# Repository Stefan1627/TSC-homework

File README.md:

# TSC-homework - Stefan Calmac 334CC
# InkTime Watch

---

## Block Diagram

```
           [ USB Type-C ]                              [ LiPo Battery (250mAh) ]
                 | 5V VBUS                                      |
                 v                                              |
          +---------------+                                     |
          |               | BAT                                 |
          |    BQ25180    |<------------------------------------+
          | (Charger IC)  |                                     |
          +---------------+                                     v
                 | VSYS                                 +---------------+
                 v                                      |   MAX17048    |
          +---------------+                             | (Fuel Gauge)  |
          |    RT6160     |                             +---------------+
          | (Buck-Boost)  |                                     ^
          +---------------+                                     |
                 | 3.3V System Rail (VDD_3V3)                   |
                 |                                              |
 +---------------+----------------------------------------------+-----+
 |               |                                              |     |
 |               v                                              |     |
 |        +-------------+         I2C Bus                       |     |
 |        |             |<======================================+     |
 |        |             |                                             |
 |        |             |=== I2C ===> [ BMA421 Accelerometer ]        |
 |        |  nRF52840   |                                             |
 |        |    MCU      |=== I2C ===> [ DRV2605L Driver ]-->[ Motor ] |
 |        |             |                                             |
 |        |             |=== SPI ===> [ 1.54" E-paper Display ]       |
 |        |             |                       ^                     |
 |        |             |-- GPIO (Gate)         | VEPD (Switched Pwr) |
 |        +-------------+      |                |                     |
 |          ^  ^  ^  |         v                |                     |
 |          |  |  |  | +---------------+        |                     |
 +---------(|--|--|)-+-|  PFET Switch  |--------+                     |
            |  |  |  | +---------------+                              |
 [Up]-------+  |  |  |                                                |
           [Down] |  +--- [ 2.4GHz Antenna ] - - - BLE - - - [ Companion ]
                  |                                          [   Phone   ]
              [Enter/Esc]
```

---

## Bill of Materials (BOM)

Below is the list of primary active and critical passive components used in this
design. Links are provided to JLCPCB parts (LCSC) and standard datasheets.

| Component / Module | Description | Package / Footprint | Part | Datasheet Link |
:--- | :--- | :--- | :--- | :--- |
| **nRF52840** | Multi-protocol BLE 5.0 Cortex-M4F MCU | AQFN-73 | [C190794](https://jlcpcb.com/partdetail/NordicSemicon-NRF52840_QIAAR/C190794) | [Nordic nRF52840](https://www.nordicsemi.com/Products/nRF52840) |
| **BQ25180YBGR** | I2C Controlled 1A Linear LiPo Charger | DSBGA-8 | [BQ25180YBGR](https://www.ti.com/product/BQ25180/part-details/BQ25180YBGR) | [TI BQ25180](https://www.ti.com/product/BQ25180) |
| **MAX17048G+T10** | Micropower 1-Cell Fuel Gauge | TDFN-8 | [C2682616](https://www.lcsc.com/product-detail/C2682616.html) | [Maxim MAX17048](https://www.analog.com/en/products/max17048.html) |
| **RT6160AWSC** | High-Efficiency Buck-Boost Converter (3.3V) | WLCSP-15 | [C7065276](https://www.lcsc.com/product-detail/C7065276.html) | [Richtek RT6160A](https://www.richtek.com/assets/product_file/RT6160A/DS6160A-02.pdf) |
| **BMA421** | Ultra-Low Power IMU / Step Counter | LGA-12 | [C5242966](https://jlcpcb.com/partdetail/BoschSensortec-BMA421/C5242966) | [Bosch BMA421](https://www.bosch-sensortec.com/products/motion-sensors/imus/bma421/) |
| **DRV2605YZFR** | Haptic Driver for LRA/ERM | DSBGA-9 | [C527464](https://jlcpcb.com/partdetail/C527464) | [TI DRV2605](https://www.ti.com/product/DRV2605) |
| **2450AT18B100E** | 2.4GHz Chip Antenna | 1206 | [C2917717](https://jlcpcb.com/partdetail/JohansonDielectrics-2450AT18B100E/C2917717) | [Johanson 2450AT18B100E](https://www.johansontechnology.com/datasheets/antennas/2450AT18B100.pdf) |
| **USBLC6-2SC6Y** | Very low capacitance ESD protection | SOT-23-6 | [C2969755](https://jlcpcb.com/partdetail/STMicroelectronics-USBLC62SC6Y/C2969755) | [ST USBLC6-2](https://www.st.com/resource/en/datasheet/usblc6-2.pdf) |
| **KH-TYPE-C-16P** | USB Type-C 16-Pin Receptacle | SMD | [C168704](https://jlcpcb.com/partdetail/180087-918418K2022Y40000/C168704) | [Generic USB-C](https://datasheet.lcsc.com/lcsc/1811151641_Korean-Hroparts-Elec-TYPE-C-31-M-12_C165948.pdf) |
| **503480-2400** | 24-Pin FPC Connector (0.5mm pitch) for EPD | SMD |  | [Molex 503480](https://www.molex.com/molex/products/part-detail/ffc_fpc_connectors/5034802400) |
| **DMG2305UX** | P-Channel MOSFET (EPD Power Control) | SOT-23 | [C2940629](https://jlcpcb.com/partdetail/TECHPUBLIC-DMG2305UX/C2940629) | [Diodes DMG2305](https://www.diodes.com/assets/Datasheets/DMG2305UX.pdf) |
| **MBR0530** | Schottky Diode (E-Paper Pump Circuit) | SOD-123 | [C77336](https://jlcpcb.com/partdetail/78464-MBR0530/C77336) | [Onsemi MBR0530](https://www.onsemi.com/pdf/datasheet/mbr0530t1-d.pdf) |
| **TC2030-IDC** | 6-Pin Tag-Connect SWD Interface | PCB Footprint | [Tag-Connect](https://www.tag-connect.com/product/tc2030-idc-nl) | [Tag-Connect TC2030](https://www.tag-connect.com/product/tc2030-idc-6-pin-tag-connect-plug-of-nails-spring-pin-cable-with-ribbon-connector) |

### Passive Components

| Component | Value | Package | Qty | Function |
|-----------|-------|---------|-----|----------|
| Capacitors (decoupling) | 100nF | 0201 | 5 | MCU + peripheral decoupling |
| Capacitors (crystal load) | 12pF | 0201 | 4 | 32MHz + 32.768kHz crystal loads |
| Capacitors (bulk) | 4.7uF | 0402 | 4 | MCU power rail bulk decoupling |
| Capacitors (USB) | 4.7uF | 0402 | 1 | DECUSB capacitor |
| Capacitors (power) | 22uF | 0402 | 2 | RT6160 input capacitors |
| Capacitors (charger) | 1uF | 0402 | 3 | BQ25180 CIN/CSYS/CBAT |
| Capacitors (EPD) | 1uF/50V | 0402 | 9 | E-paper driver capacitors |
| Inductor (DC/DC) | 10uH | 0402 | 1 | nRF52840 REG1 DC/DC inductor |
| Inductor (buck-boost) | 0.47uH | 2012 | 1 | RT6160 power stage inductor |
| Resistors (I2C pull-up) | 10k | 0201 | 2 | I2C SDA/SCL pull-ups |
| Resistors (USB CC) | 5.1k | 0201 | 2 | USB Type-C CC1/CC2 pull-downs |
| Crystals | 32 MHz | 2016 | 1 | HFXO for MCU + radio |
| Crystals | 32.768 kHz | 3215 | 1 | LFXO for RTC timekeeping |

---

## Hardware Description

### MCU - nRF52840

The nRF52840 is the central processing unit of InkTime. It integrates:

- **ARM Cortex-M4F** at 64 MHz with FPU
- **BLE 5.0** (used for time sync, notifications)
- **USB 2.0 Full Speed** (charging detection and firmware updates)
- **1 MB Flash / 256 KB RAM**

All peripherals are connected directly to the nRF52840 via SPI (e-paper display) and I2C (IMU, fuel gauge, haptic driver, PMIC).

### Power Path

```
USB-C --> BQ25180 (charger) --> LiPo battery (AKY0106, 400 mAh)
                            --> 3.3V rail (VREG, for MCU and all peripherals)
Battery --> RT6160AWSC (boost) --> EPD high-voltage supply (VCOM, gate voltages)
```

- **BQ25180YBGR** manages LiPo charging at up to 1A, monitors VBUS, and raises `PMIC_INT` for fault/status events. Communicates with the MCU over I2C.
- **RT6160AWSC** is a boost converter that generates the higher voltages needed by the e-paper display driver (PREVGH, PREVGL, etc.).
- **MAX17048G+T10** is a ModelGauge fuel gauge that estimates battery state-of-charge (SOC) with 1% accuracy over I2C, using a single-cell LiPo model.

### E-Paper Display - WSH-12561

The e-paper display connects to the MCU over **SPI** plus 3 control GPIOs:

| Signal   | Direction | Description                 |
| -------- | --------- | --------------------------- |
| SCK      | MCU → EPD | SPI clock                   |
| MOSI     | MCU → EPD | SPI data                    |
| EPD_CS   | MCU → EPD | Chip select (active low)    |
| EPD_DC   | MCU → EPD | Data / Command select       |
| EPD_RST  | MCU → EPD | Hardware reset (active low) |
| EPD_BUSY | EPD → MCU | Busy flag (MCU must wait)   |

The EPD drive circuit (biased by RT6160AWSC) generates the voltages PREVGH, PREVGL, PREVGL, GDR necessary to drive the e-paper panel.

### IMU

6-axis inertial measurement unit connected via **I2C** at 400 kHz. Provides:

- 3-axis accelerometer (step counting, gesture detection, orientation)
- 3-axis gyroscope (motion tracking)
- Two interrupt lines (`IMU_INT1`, `IMU_INT2`) for wake-on-motion and data-ready events

### Haptic Feedback - DRV2605 + FIT0774

The DRV2605YZFR haptic driver controls the FIT0774 ERM motor. It connects to the MCU over **I2C** and has a digital enable signal `HAPTIC_EN`. It supports library-based waveform playback (124 built-in effects).

### USB - KH-TYPE-C-16P + USBLC6-2SC6Y

USB-C connector with USBLC6-2SC6Y ESD protection on D+ and D− lines. The MCU detects VBUS presence via a GPIO for charging control handoff. USB D+ / D− connect directly to the nRF52840's USB transceiver.

### Antenna - 2450AT18B100E

2.4 GHz chip antenna placed at the PCB edge, away from metal and ground planes. The PCB is **cutout under the antenna** - no copper pours or signal traces are routed under the antenna keepout area. Impedance matching network (L + C pi filter) is present between the nRF52840 RF pin and the antenna.

### SWD Debug - TC2030-IDC

Tag-Connect TC2030-IDC footprint for in-circuit programming and debugging (no connector needed, uses spring-loaded probe). Test pads TP_SWDIO, TP_SWDCLK, TP_RESET, TP_3.3V, TP_GND are exposed on the PCB silkscreen.

---

## nRF52840 Pinout Specification
The major hardware peripherals are mapped to the MCU as follows:

*   **Shared I2C Bus (with 10k pull-ups to 3.3V):**
    *   `P0.06` - SDA (Data for BMA421, MAX17048, BQ25180, RT6160, DRV2605L).
    *   `P0.07` - SCL (Clock).
*   **SPI Bus (E-paper Display):**
    *   `P0.02` - SCK
    *   `P0.03` - MOSI
    *   `P0.05` - CS (Chip Select)
    *   `P0.15` - DC (Data/Command)
    *   `P0.16` - RST (Reset)
    *   `P0.17` - BUSY (Panel status)
    *   `P1.01` - PFET Gate (Enables/disables the display power rail)
*   **Interrupts & Peripherals:**
    *   `P0.08` - BMA421 INT1 (Primary motion/step wake).
    *   `P1.08` - BMA421 INT2 (Secondary motion events).
    *   `P0.10` - MAX17048 ALRT (Low battery wake).
    *   `P0.11` - BQ25180 /INT (Charger state wake).
    *   `P0.12` - DRV2605L EN (Enable haptics chip).
*   **Physical Buttons (Active-low to GND):**
    *   `P0.13` - Up Button.
    *   `P0.14` - Down Button.
    *   `P1.00` - Enter / Esc Button.
*   **Debug & Clocks:**
    *   `XC1/XC2` & `XL1/XL2` - Connects the 32MHz and 32.768kHz external crystals.
    *   `SWDIO`, `SWDCLK`, `nRESET` - Connected to the Tag-Connect TC2030 debug footprint.

--- 

## PCB Design

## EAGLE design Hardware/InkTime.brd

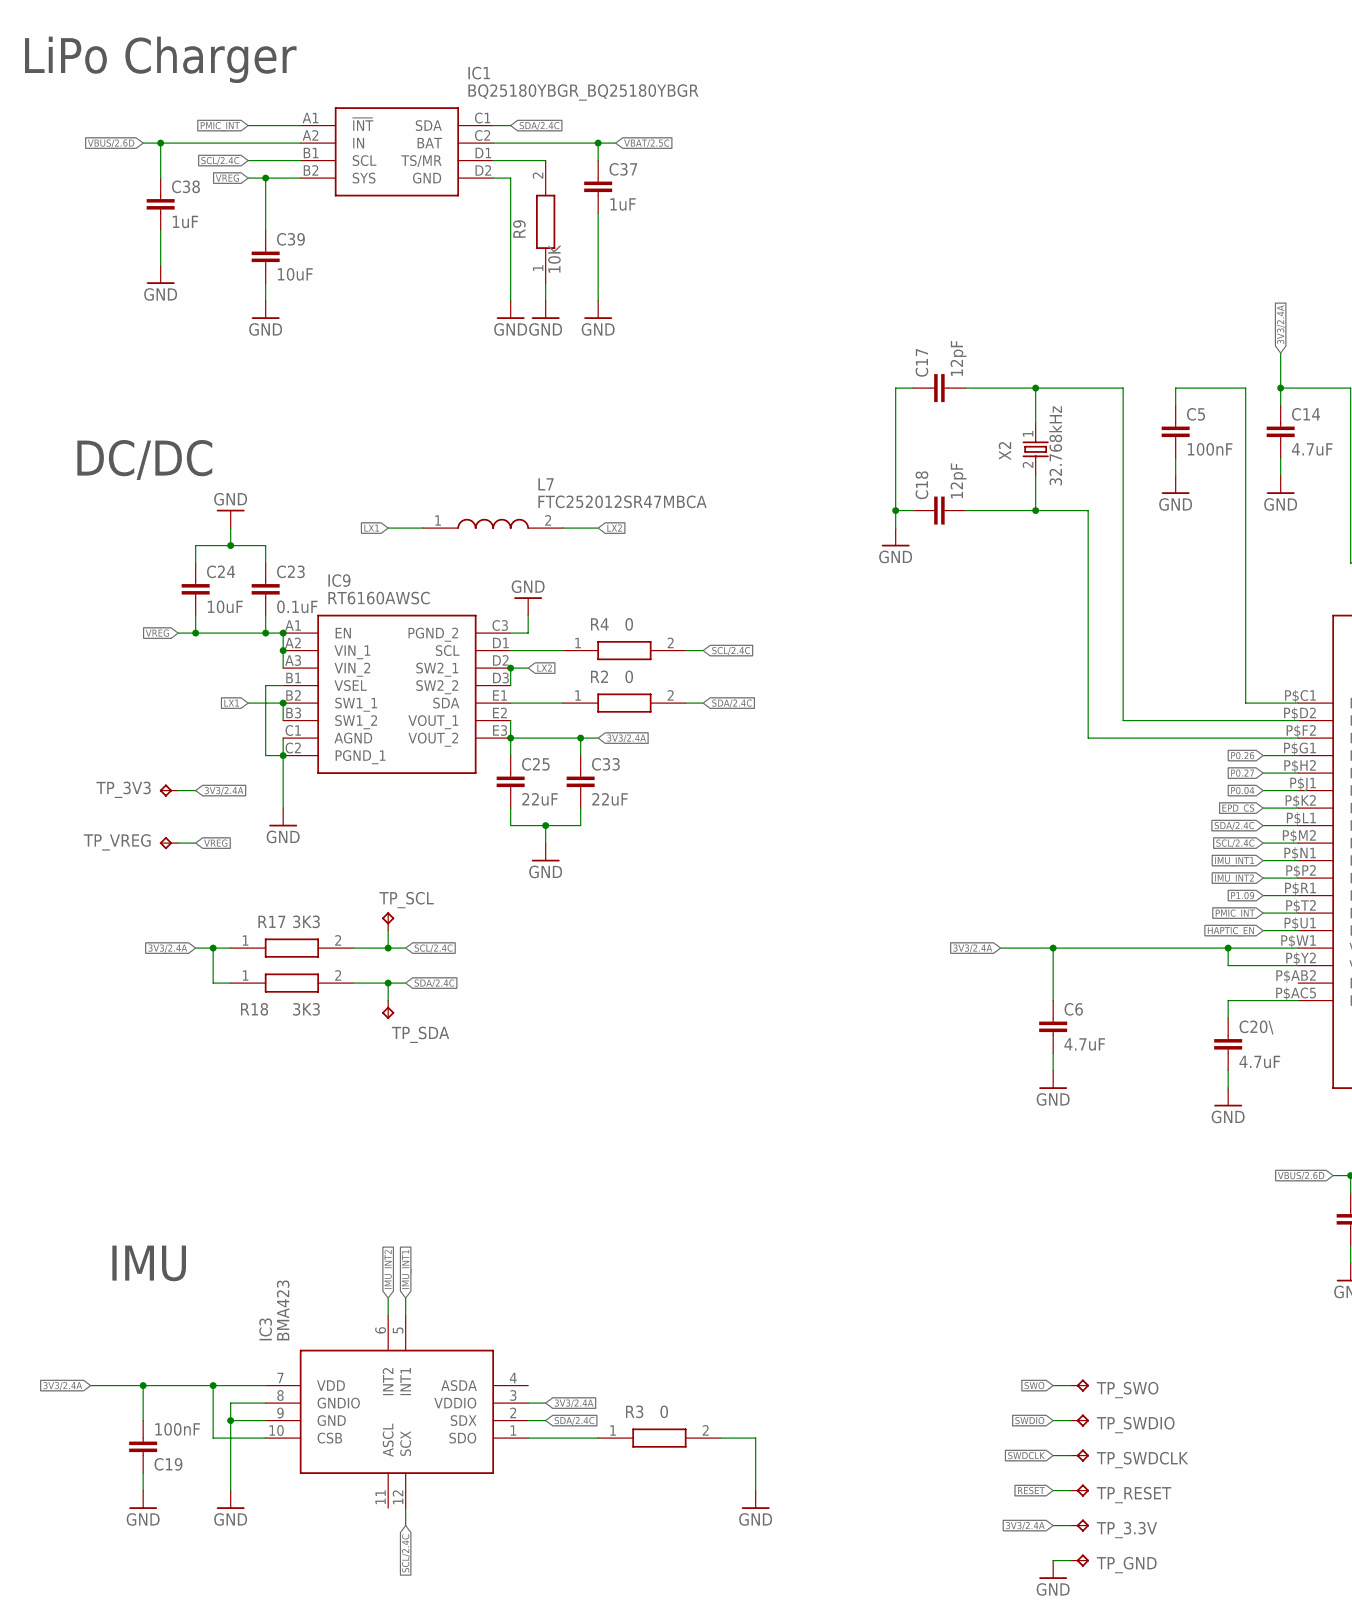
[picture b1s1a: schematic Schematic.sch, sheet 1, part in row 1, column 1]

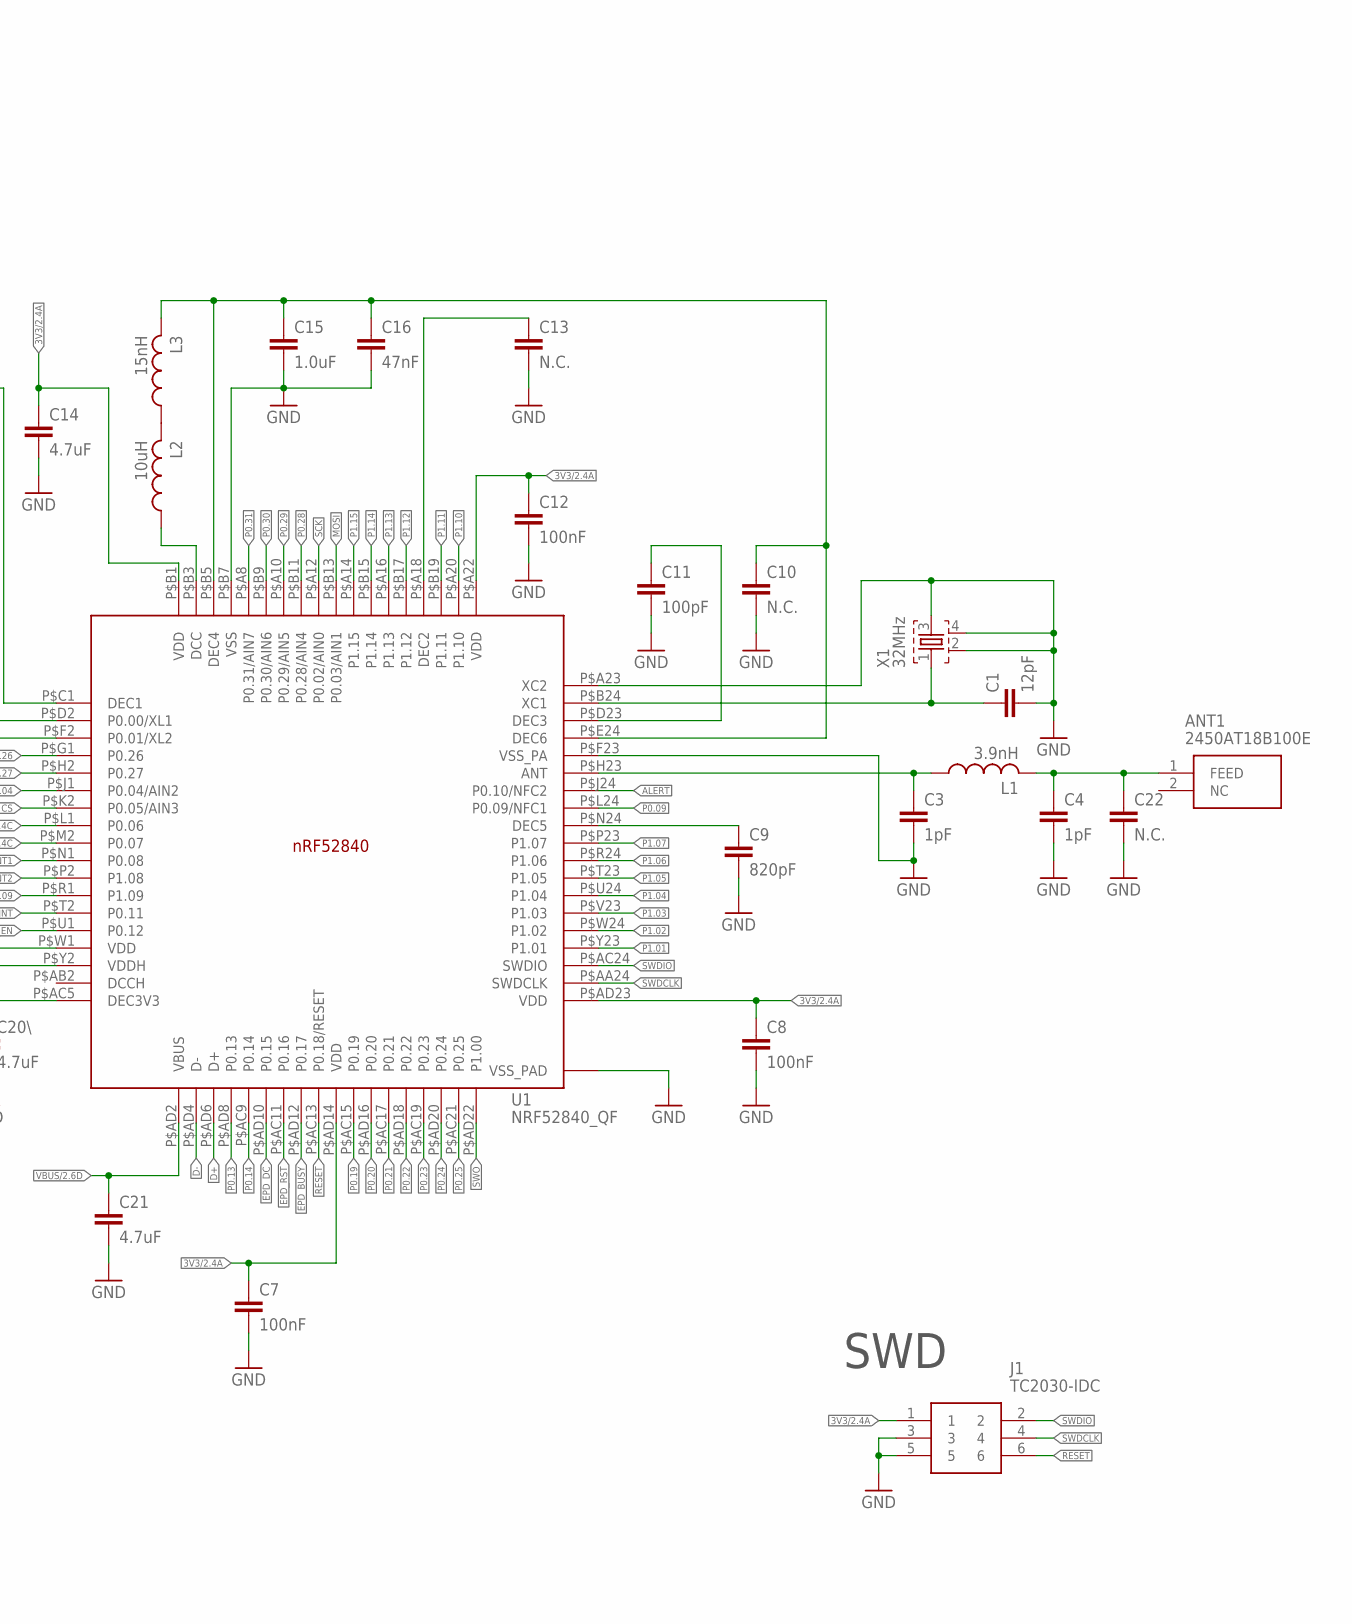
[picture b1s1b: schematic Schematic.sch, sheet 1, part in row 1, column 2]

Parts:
ANT1: 2450AT18B100E; 2450AT18B100E_ANTC3216X140N
C1, C17, C18: 12pF; NORDIC_NRF_3_RESC0201_L
C3, C4: 1pF; NORDIC_NRF_3_RESC0201_L
C5, C7, C8, C12, C19: 100nF; NORDIC_NRF_3_RESC0201_L
C6, C14, C20\, C21: 4.7uF; NORDIC_NRF_3_RESC0402_L
C9: 820pF; NORDIC_NRF_3_RESC0201_L
C10, C13, C22: N.C.; NORDIC_NRF_3_RESC0201_L
C11: 100pF; NORDIC_NRF_3_RESC0201_L
C15: 1.0uF; NORDIC_NRF_3_RESC0402_L
C16: 47nF; NORDIC_NRF_3_RESC0201_L
C23: 0.1uF; NORDIC_NRF_3_RESC0201_L
C24, C39: 10uF; NORDIC_NRF_3_RESC0402_L
C25, C33: 22uF; NORDIC_NRF_3_RESC0402_L
C37, C38: 1uF; NORDIC_NRF_3_RESC0402_L
IC1: BQ25180YBGR_BQ25180YBGR; BQ25180YBGR_BGA8C40P2X4_100X155X50
IC3: BMA423; BMA423_BMA423
IC9: RT6160AWSC; RT6160AWSC_BGA15C40P3X5_140X230X60
J1: TC2030-IDC; TC2030-IDC_TC2030IDC
L1: 3.9nH; NORDIC_NRF_2_RESC0402_L
L2: 10uH; NORDIC_NRF_2_RESC0402_L
L3: 15nH; NORDIC_NRF_2_RESC0402_L
L7: FTC252012SR47MBCA; MLP2016SR47MT0S1_INDC2016X100N
R2, R3, R4: 0; CPF0201D7K68C1_0201
R9: 10K; CPF0201D7K68C1_0201
R17, R18: 3K3; CPF0201D7K68C1_0201
TP_3.3V, TP_3V3: HECTOR_WATCH_1_TPTP20R; HECTOR_WATCH_1_TP20R
TP_GND: HECTOR_WATCH_1_TPTP20R; HECTOR_WATCH_1_TP20R
TP_RESET: HECTOR_WATCH_1_TPTP20R; HECTOR_WATCH_1_TP20R
TP_SCL: HECTOR_WATCH_1_TPTP20R; HECTOR_WATCH_1_TP20R
TP_SDA: HECTOR_WATCH_1_TPTP20R; HECTOR_WATCH_1_TP20R
TP_SWDCLK: HECTOR_WATCH_1_TPTP20R; HECTOR_WATCH_1_TP20R
TP_SWDIO: HECTOR_WATCH_1_TPTP20R; HECTOR_WATCH_1_TP20R
TP_SWO: HECTOR_WATCH_1_TPTP20R; HECTOR_WATCH_1_TP20R
TP_VREG: HECTOR_WATCH_1_TPTP20R; HECTOR_WATCH_1_TP20R
U1: NRF52840_QF; NORDIC_NRF_4_AQFN50P700X700X85_HS-74N
X1: 32MHz; NORDIC_NRF_BT-XTAL_2016_N
X2: 32.768kHz; NORDIC_NRF_1_XTAL_3215_N

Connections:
3V3/2.4A: C6.1, C7.2, C8.2, C12.2, C14.1, C19.2, C25.1, C33.1, IC3.3 (VDDIO), IC3.7 (VDD), IC3.10 (CSB), IC9.E2 (VOUT_1), IC9.E3 (VOUT_2), J1.1, R17.1, R18.1, TP_3.3V.TP, TP_3V3.TP, U1.P$A22 (VDD), U1.P$AD14 (VDD), U1.P$AD23 (VDD), U1.P$B1 (VDD), U1.P$W1 (VDD), U1.P$Y2 (VDDH)
ALERT: U1.P$J24 (P0.10/NFC2); also elsewhere on the board
D+: U1.P$AD6 (D+); also elsewhere on the board
D-: U1.P$AD4 (D-); also elsewhere on the board
EPD_BUSY: U1.P$AD12 (P0.17); also elsewhere on the board
EPD_CS: U1.P$K2 (P0.05/AIN3); also elsewhere on the board
EPD_DC: U1.P$AD10 (P0.15); also elsewhere on the board
EPD_RST: U1.P$AC11 (P0.16); also elsewhere on the board
GND: C1.1, C3.1, C4.1, C5.1, C6.2, C7.1, C8.1, C9.1, C10.1, C11.1, C12.1, C13.1, C14.2, C15.2, C16.1, C17.1, C18.1, C19.1, C20\.2, C21.2, C22.1, C23.1, C24.1, C25.2, C33.2, C37.2, C38.2, C39.2, IC1.D2 (GND), IC3.8 (GNDIO), IC3.9 (GND), IC9.B1 (VSEL), IC9.C1 (AGND), IC9.C2 (PGND_1), IC9.C3 (PGND_2), J1.3, J1.5, R3.2, R9.1, TP_GND.TP, U1.P$74 (VSS_PAD), U1.P$75 (VSS_PAD), U1.P$76 (VSS_PAD), U1.P$77 (VSS_PAD), U1.P$78 (VSS_PAD), U1.P$79 (VSS_PAD), U1.P$80 (VSS_PAD), U1.P$81 (VSS_PAD), U1.P$82 (VSS_PAD), U1.P$83 (VSS_PAD), U1.P$84 (VSS_PAD), U1.P$85 (VSS_PAD), U1.P$86 (VSS_PAD), U1.P$87 (VSS_PAD), U1.P$88 (VSS_PAD), U1.P$89 (VSS_PAD), U1.P$90 (VSS_PAD), U1.P$A23 (XC2), U1.P$B7 (VSS), U1.P$F23 (VSS_PA), X1.2, X1.3, X1.4; also elsewhere on the board
HAPTIC_EN: U1.P$U1 (P0.12); also elsewhere on the board
IMU_INT1: IC3.5 (INT1), U1.P$N1 (P0.08)
IMU_INT2: IC3.6 (INT2), U1.P$P2 (P1.08)
LX1: IC9.B2 (SW1_1), IC9.B3 (SW1_2), L7.1
LX2: IC9.D2 (SW2_1), IC9.D3 (SW2_2), L7.2
MOSI: U1.P$B13 (P0.03/AIN1); also elsewhere on the board
unnamed: IC9.E1 (SDA), R2.1
unnamed: IC1.D1 (TS/MR), R9.2
unnamed: IC9.D1 (SCL), R4.1
unnamed: C9.2, U1.P$N24 (DEC5)
unnamed: IC3.1 (SDO), R3.1
unnamed: C1.2, U1.P$B24 (XC1), X1.1
unnamed: C3.2, L1.1, U1.P$H23 (ANT)
unnamed: C11.2, U1.P$D23 (DEC3)
unnamed: C17.2, U1.P$D2 (P0.00/XL1), X2.1
unnamed: C13.2, U1.P$A18 (DEC2)
unnamed: C10.2, C15.1, C16.2, L3.2, U1.P$B5 (DEC4), U1.P$E24 (DEC6)
unnamed: L2.2, L3.1
unnamed: L2.1, U1.P$B3 (DCC)
unnamed: C20\.1, U1.P$AC5 (DEC3V3)
unnamed: C5.2, U1.P$C1 (DEC1)
unnamed: C18.2, U1.P$F2 (P0.01/XL2), X2.2
P0.04: U1.P$J1 (P0.04/AIN2)
P0.09: U1.P$L24 (P0.09/NFC1)
P0.13: U1.P$AD8 (P0.13); also elsewhere on the board
P0.14: U1.P$AC9 (P0.14); also elsewhere on the board
P0.19: U1.P$AC15 (P0.19)
P0.20: U1.P$AD16 (P0.20)
P0.21: U1.P$AC17 (P0.21)
P0.22: U1.P$AD18 (P0.22)
P0.23: U1.P$AC19 (P0.23)
P0.24: U1.P$AD20 (P0.24)
P0.25: U1.P$AC21 (P0.25)
P0.26: U1.P$G1 (P0.26)
P0.27: U1.P$H2 (P0.27)
P0.28: U1.P$B11 (P0.28/AIN4)
P0.29: U1.P$A10 (P0.29/AIN5)
P0.30: U1.P$B9 (P0.30/AIN6)
P0.31: U1.P$A8 (P0.31/AIN7)
P1.01: U1.P$Y23 (P1.01); also elsewhere on the board
P1.02: U1.P$W24 (P1.02); also elsewhere on the board
P1.03: U1.P$V23 (P1.03)
P1.04: U1.P$U24 (P1.04)
P1.05: U1.P$T23 (P1.05)
P1.06: U1.P$R24 (P1.06)
P1.07: U1.P$P23 (P1.07)
P1.09: U1.P$R1 (P1.09)
P1.10: U1.P$A20 (P1.10)
P1.11: U1.P$B19 (P1.11)
P1.12: U1.P$B17 (P1.12)
P1.13: U1.P$A16 (P1.13)
P1.14: U1.P$B15 (P1.14)
P1.15: U1.P$A14 (P1.15)
PMIC_INT: IC1.A1 (!INT), U1.P$T2 (P0.11)
RESET: J1.6, TP_RESET.TP, U1.P$AC13 (P0.18/RESET)
RF: ANT1.1 (FEED), C4.2, C22.2, L1.2
SCK: U1.P$A12 (P0.02/AIN0); also elsewhere on the board
SCL/2.4C: IC1.B1 (SCL), IC3.12 (SCX), R4.2, R17.2, TP_SCL.TP, U1.P$M2 (P0.07)
SDA/2.4C: IC1.C1 (SDA), IC3.2 (SDX), R2.2, R18.2, TP_SDA.TP, U1.P$L1 (P0.06)
SWDCLK: J1.4, TP_SWDCLK.TP, U1.P$AA24 (SWDCLK)
SWDIO: J1.2, TP_SWDIO.TP, U1.P$AC24 (SWDIO)
SWO: TP_SWO.TP, U1.P$AD22 (P1.00)
VBAT/2.5C: C37.1, IC1.C2 (BAT)
VBUS/2.6D: C21.1, C38.1, IC1.A2 (IN), U1.P$AD2 (VBUS)
VREG: C23.2, C24.2, C39.1, IC1.B2 (SYS), IC9.A1 (EN), IC9.A2 (VIN_1), IC9.A3 (VIN_2), TP_VREG.TP

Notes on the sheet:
LiPo Charger
DC/DC
IMU
SWD

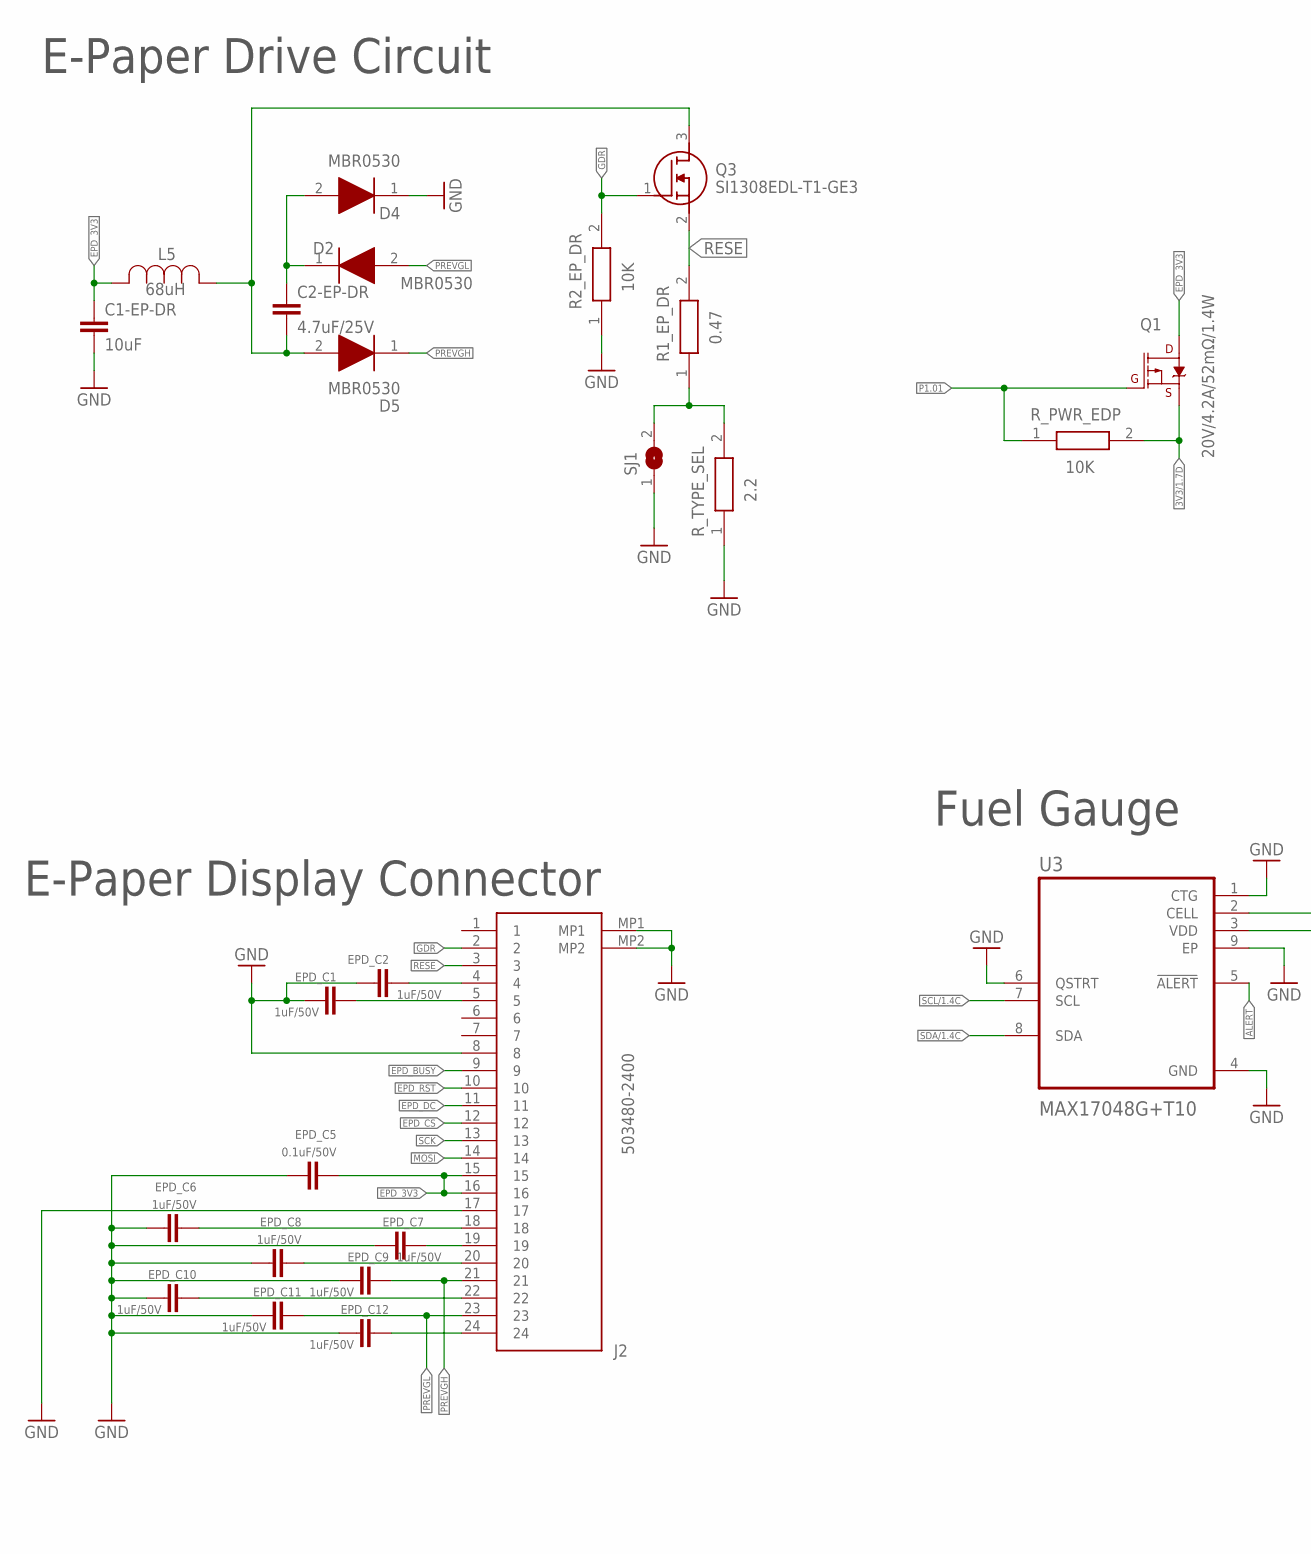
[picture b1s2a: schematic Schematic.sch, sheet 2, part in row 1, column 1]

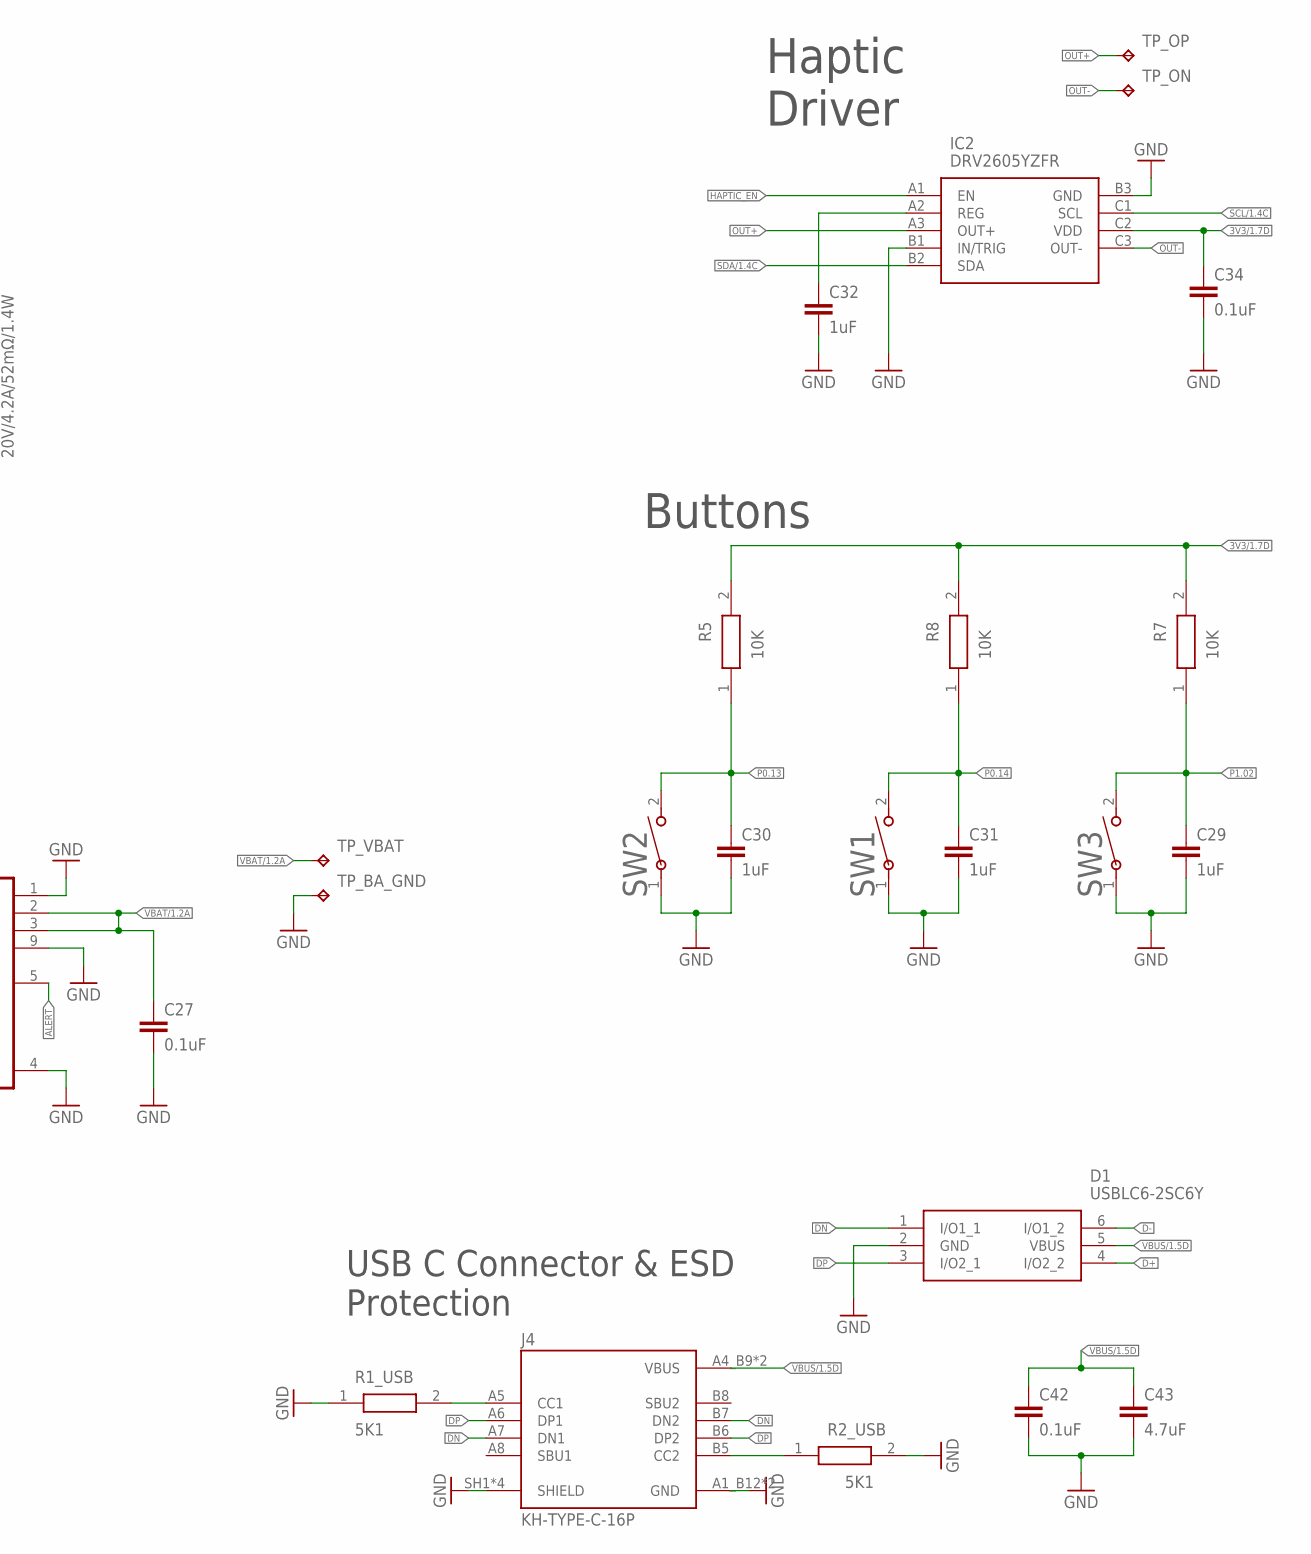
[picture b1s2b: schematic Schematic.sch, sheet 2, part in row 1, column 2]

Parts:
C1-EP-DR: 10uF; NORDIC_NRF_3_RESC0402_L
C2-EP-DR: 4.7uF/25V; NORDIC_NRF_3_RESC0402_L
C27, C34, C42: 0.1uF; NORDIC_NRF_3_RESC0201_L
C29, C30, C31, C32: 1uF; NORDIC_NRF_3_RESC0402_L
C43: 4.7uF; NORDIC_NRF_3_RESC0402_L
D1: USBLC6-2SC6Y; SOT95P280X145-6N
D2, D4, D5: MBR0530; ESP32_C6_LIBRARY_5_SOD3716X135N
EPD_C1, EPD_C2, EPD_C6, EPD_C7, EPD_C8, EPD_C9, EPD_C10, EPD_C11, EPD_C12: 1uF/50V; NORDIC_NRF_3_RESC0402_L
EPD_C5: 0.1uF/50V; NORDIC_NRF_3_RESC0201_L
IC2: DRV2605YZFR; DRV2605YZFR_BGA9C50P3X3_144X144X62
J2: 503480-2400; 503480-2400_5034802400
J4: KH-TYPE-C-16P; KH-TYPE-C-16P_KINGHELM_KH-TYPE-C-16P
L5: 68uH; ESP32_C6_LIBRARY_2_IND_4828-WE-TPC_WRE
Q1: 20V/4.2A/52mΩ/1.4W; ESP32_C6_LIBRARY_4_ESP32_C6_LIBRARY_4_ESP32_C6_LIBRARY_4_ES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
Q3: SI1308EDL-T1-GE3; ESP32_C6_LIBRARY_6_SOT65P210X110-3N
R1_EP_DR: 0.47; CPF0201D7K68C1_0201
R1_USB, R2_USB: 5K1; CPF0201D7K68C1_0201
R2_EP_DR, R5, R7, R8: 10K; CPF0201D7K68C1_0201
R_PWR_EDP: 10K; CPF0201D7K68C1_0201
R_TYPE_SEL: 2.2; CPF0201D7K68C1_0201
SJ1: ESP32_C6_LIBRARY_7_JUMPER_SJ
SW1, SW2, SW3: 2025-10-22_07-23-44_LIBRARY_EVP-AKE31ASW_EVP-AKE3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; 2025-10-22_07-23-44_LIBRARY_SW_EVP-AKE31A_PAN
TP_BA_GND: HECTOR_WATCH_1_TPTP20R; HECTOR_WATCH_1_TP20R
TP_ON: HECTOR_WATCH_1_TPTP20R; HECTOR_WATCH_1_TP20R
TP_OP: HECTOR_WATCH_1_TPTP20R; HECTOR_WATCH_1_TP20R
TP_VBAT: HECTOR_WATCH_1_TPTP20R; HECTOR_WATCH_1_TP20R
U3: MAX17048G+T10; ESP32_C6_LIBRARY_SON50P200X200X80-9N

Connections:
3V3/1.7D: C34.1, IC2.C2 (VDD), Q1.2 (S), R5.2, R7.2, R8.2, R_PWR_EDP.2
ALERT: U3.5 (!ALERT); also elsewhere on the board
D+: D1.4 (I/O2_2); also elsewhere on the board
D-: D1.6 (I/O1_2); also elsewhere on the board
DN: D1.1 (I/O1_1), J4.A7 (DN1), J4.B7 (DN2)
DP: D1.3 (I/O2_1), J4.A6 (DP1), J4.B6 (DP2)
EPD_3V3: C1-EP-DR.1, EPD_C5.2, J2.15, J2.16, L5.2, Q1.3 (D)
EPD_BUSY: J2.9; also elsewhere on the board
EPD_CS: J2.12; also elsewhere on the board
EPD_DC: J2.11; also elsewhere on the board
EPD_RST: J2.10; also elsewhere on the board
GDR: J2.2, Q3.1 (G), R2_EP_DR.2
GND: C1-EP-DR.2, C27.2, C29.2, C30.2, C31.2, C32.2, C34.2, C42.2, C43.2, D1.2 (GND), D4.1 (K), EPD_C1.1, EPD_C2.1, EPD_C5.1, EPD_C6.1, EPD_C7.1, EPD_C8.1, EPD_C9.1, EPD_C10.1, EPD_C11.1, EPD_C12.1, IC2.B1 (IN/TRIG), IC2.B3 (GND), J2.8, J2.17, J2.MP1, J2.MP2, J4.A1_B12 (GND), J4.A12_B1 (GND), J4.SH1 (SHIELD), J4.SH2 (SHIELD), J4.SH3 (SHIELD), J4.SH4 (SHIELD), R1_USB.1, R2_EP_DR.1, R2_USB.2, R_TYPE_SEL.1, SJ1.1, SW1.1, SW2.1, SW3.1, TP_BA_GND.TP, U3.1 (CTG), U3.4 (GND), U3.6 (QSTRT), U3.9 (EP); also elsewhere on the board
HAPTIC_EN: IC2.A1 (EN); also elsewhere on the board
MOSI: J2.14; also elsewhere on the board
unnamed: C2-EP-DR.2, D5.2 (A), L5.1, Q3.3 (D)
unnamed: R1_EP_DR.1, R_TYPE_SEL.2, SJ1.2
unnamed: C2-EP-DR.1, D2.1 (K), D4.2 (A)
unnamed: EPD_C2.2, J2.4
unnamed: EPD_C1.2, J2.5
unnamed: C32.1, IC2.A2 (REG)
unnamed: EPD_C6.2, J2.18
unnamed: EPD_C7.2, J2.19
unnamed: EPD_C8.2, J2.20
unnamed: J4.B5 (CC2), R2_USB.1
unnamed: EPD_C10.2, J2.22
unnamed: EPD_C12.2, J2.24
unnamed: J4.A5 (CC1), R1_USB.2
OUT+: IC2.A3 (OUT+), TP_OP.TP
OUT-: IC2.C3 (OUT-), TP_ON.TP
P0.13: C30.1, R5.1, SW2.2; also elsewhere on the board
P0.14: C31.1, R8.1, SW1.2; also elsewhere on the board
P1.01: Q1.1 (G), R_PWR_EDP.1; also elsewhere on the board
P1.02: C29.1, R7.1, SW3.2; also elsewhere on the board
PREVGH: D5.1 (K), EPD_C9.2, J2.21
PREVGL: D2.2 (A), EPD_C11.2, J2.23
RESE: J2.3, Q3.2 (S), R1_EP_DR.2
SCK: J2.13; also elsewhere on the board
SCL/1.4C: IC2.C1 (SCL), U3.7 (SCL)
SDA/1.4C: IC2.B2 (SDA), U3.8 (SDA)
VBAT/1.2A: C27.1, TP_VBAT.TP, U3.2 (CELL), U3.3 (VDD)
VBUS/1.5D: C42.1, C43.1, D1.5 (VBUS), J4.A4_B9 (VBUS), J4.A9_B4 (VBUS)

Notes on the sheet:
E-Paper Drive Circuit
Haptic Driver
Buttons
USB C Connector & ESD Protection
Fuel Gauge
E-Paper Display Connector

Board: 4 copper layers, 104 parts (0 on the bottom side), 74 nets, no tracks yet.

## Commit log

2026-03-14 Add Apache License 2.0
    Added the Apache License Version 2.0 to the project.
2026-03-15 Schematic first try
2026-04-10 Added files for review
2026-04-10 3d + images
2026-04-16 Update 2d pcb
2026-04-19 Update PCB
2026-04-20 Add PCB design, manufacturing files and docs
2026-04-21 Update routes width
2026-04-21 Add PCB design photos to README
    Added images of the PCB layers and 3D view to the README.
2026-04-21 Update Images
2026-04-21 Update 3D PCB image in README
2026-04-21 update 3d
2026-04-21 update image

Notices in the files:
parts and their libraries:
COPYRIGHT: Copyright (C) 2024 Ultra Librarian. All rights reserved.
COPYRIGHT: Copyright (C) 2025 Ultra Librarian. All rights reserved.
